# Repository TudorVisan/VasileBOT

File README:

VasileBOT! LineFollower extraordinaire!

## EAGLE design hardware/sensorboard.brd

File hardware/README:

v1.0
    - Complete BOM available at
      https://docs.google.com/spreadsheets/d/1lKYWt8WgzWd33CoD_yIm1lVHJigqv4kNXPXV9A-a3yk/edit?usp=sharing

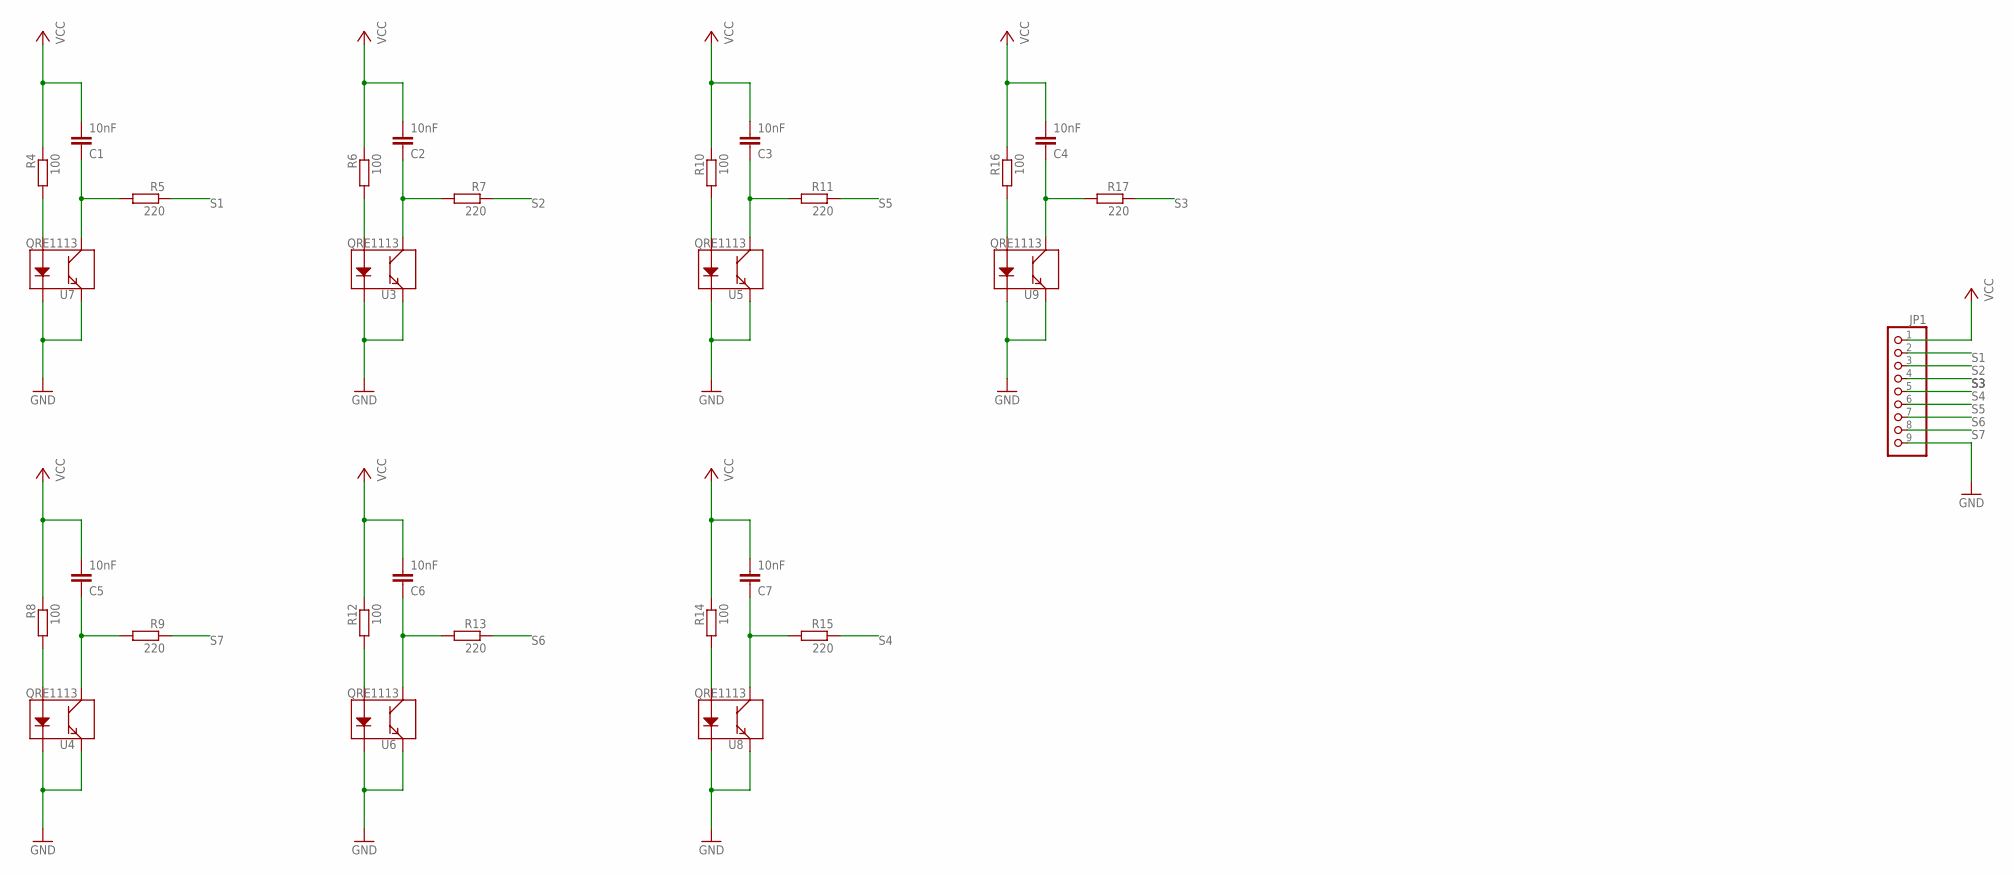
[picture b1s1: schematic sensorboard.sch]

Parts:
C1, C2, C3, C4, C5, C6, C7: 10nF; C0805K
JP1: PINHD-1X9; 1X09
R4, R6, R8, R10, R12, R14, R16: 100; M0805
R5, R7, R9, R11, R13, R15, R17: 220; M0805
U3, U4, U5, U6, U7, U8, U9: QRE1113

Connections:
GND: JP1.9, U3.2 (K), U3.4 (E), U4.2 (K), U4.4 (E), U5.2 (K), U5.4 (E), U6.2 (K), U6.4 (E), U7.2 (K), U7.4 (E), U8.2 (K), U8.4 (E), U9.2 (K), U9.4 (E)
unnamed: C1.1, R5.2, U7.3 (C)
unnamed: C2.1, R7.2, U3.3 (C)
unnamed: C3.1, R11.2, U5.3 (C)
unnamed: C4.1, R17.2, U9.3 (C)
unnamed: C7.1, R15.2, U8.3 (C)
unnamed: C6.1, R13.2, U6.3 (C)
unnamed: C5.1, R9.2, U4.3 (C)
unnamed: R4.2, U7.1 (A)
unnamed: R6.2, U3.1 (A)
unnamed: R8.2, U4.1 (A)
unnamed: R10.2, U5.1 (A)
unnamed: R12.2, U6.1 (A)
unnamed: R14.2, U8.1 (A)
unnamed: R16.2, U9.1 (A)
S1: JP1.2, R5.1
S2: JP1.3, R7.1
S3: JP1.4, R17.1
S4: JP1.5, R15.1
S5: JP1.6, R11.1
S6: JP1.7, R13.1
S7: JP1.8, R9.1
VCC: C1.2, C2.2, C3.2, C4.2, C5.2, C6.2, C7.2, JP1.1, R4.1, R6.1, R8.1, R10.1, R12.1, R14.1, R16.1

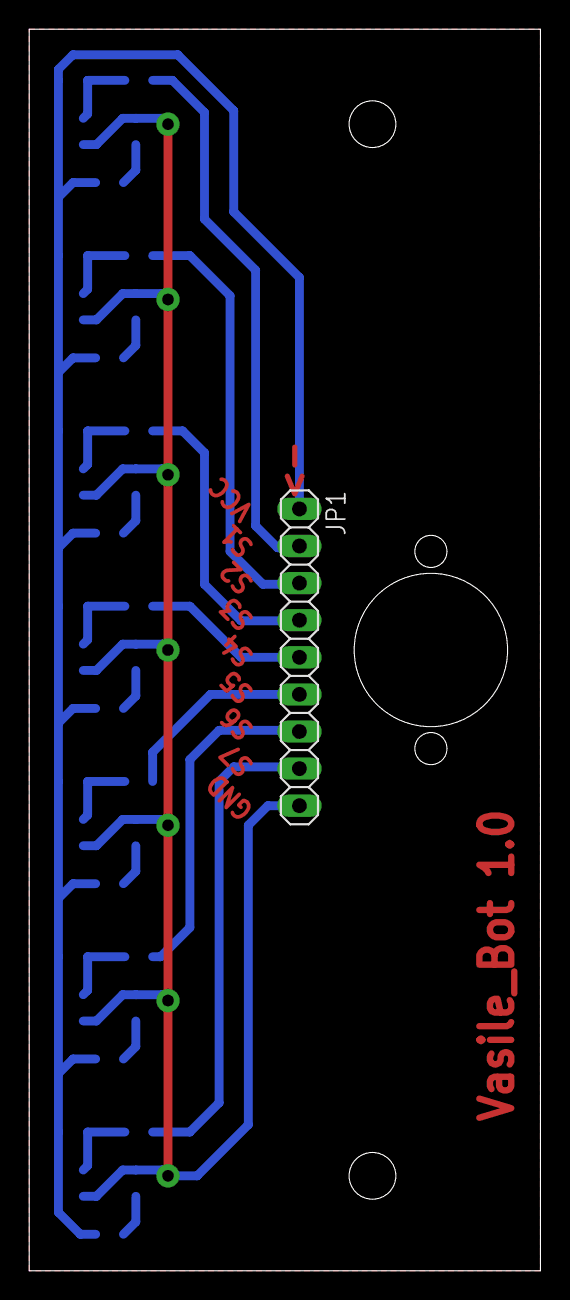
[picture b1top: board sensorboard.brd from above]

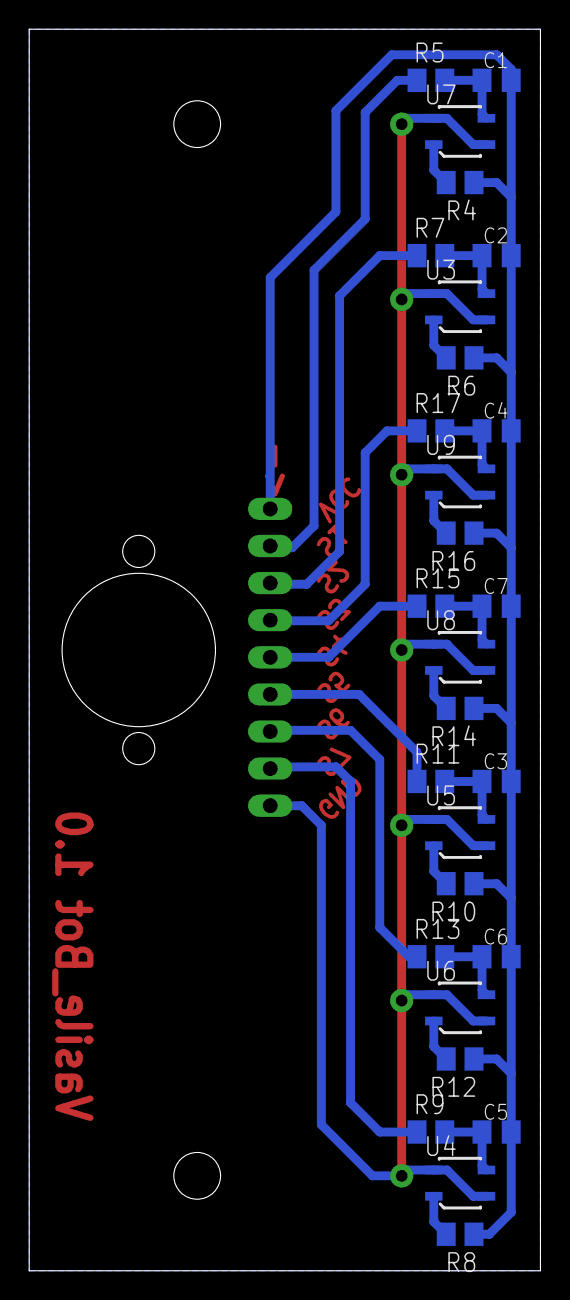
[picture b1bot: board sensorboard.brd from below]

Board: 2 copper layers, 35.0 x 85.0 mm, 29 parts (28 on the bottom side), 23 nets.

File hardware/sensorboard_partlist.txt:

Partlist

Exported from sensorboard.sch at 08/11/2016 20:00

EAGLE Version 7.6.0 Copyright (c) 1988-2016 CadSoft

Assembly variant: 

Part     Value          Device     Package  Library          Sheet

C1       10nF           C-EUC0805K C0805K   resistor         1
C2       10nF           C-EUC0805K C0805K   resistor         1
C3       10nF           C-EUC0805K C0805K   resistor         1
C4       10nF           C-EUC0805K C0805K   resistor         1
C5       10nF           C-EUC0805K C0805K   resistor         1
C6       10nF           C-EUC0805K C0805K   resistor         1
C7       10nF           C-EUC0805K C0805K   resistor         1
JP1                     PINHD-1X9  1X09     pinhead          1
R4       100            R-EU_M0805 M0805    resistor         1
R5       220            R-EU_M0805 M0805    resistor         1
R6       100            R-EU_M0805 M0805    resistor         1
R7       220            R-EU_M0805 M0805    resistor         1
R8       100            R-EU_M0805 M0805    resistor         1
R9       220            R-EU_M0805 M0805    resistor         1
R10      100            R-EU_M0805 M0805    resistor         1
R11      220            R-EU_M0805 M0805    resistor         1
R12      100            R-EU_M0805 M0805    resistor         1
R13      220            R-EU_M0805 M0805    resistor         1
R14      100            R-EU_M0805 M0805    resistor         1
R15      220            R-EU_M0805 M0805    resistor         1
R16      100            R-EU_M0805 M0805    resistor         1
R17      220            R-EU_M0805 M0805    resistor         1
U3       QRE1113        QRE1113    QRE1113  SparkFun-Sensors 1
U4       QRE1113        QRE1113    QRE1113  SparkFun-Sensors 1
U5       QRE1113        QRE1113    QRE1113  SparkFun-Sensors 1
U6       QRE1113        QRE1113    QRE1113  SparkFun-Sensors 1
U7       QRE1113        QRE1113    QRE1113  SparkFun-Sensors 1
U8       QRE1113        QRE1113    QRE1113  SparkFun-Sensors 1
U9       QRE1113        QRE1113    QRE1113  SparkFun-Sensors 1

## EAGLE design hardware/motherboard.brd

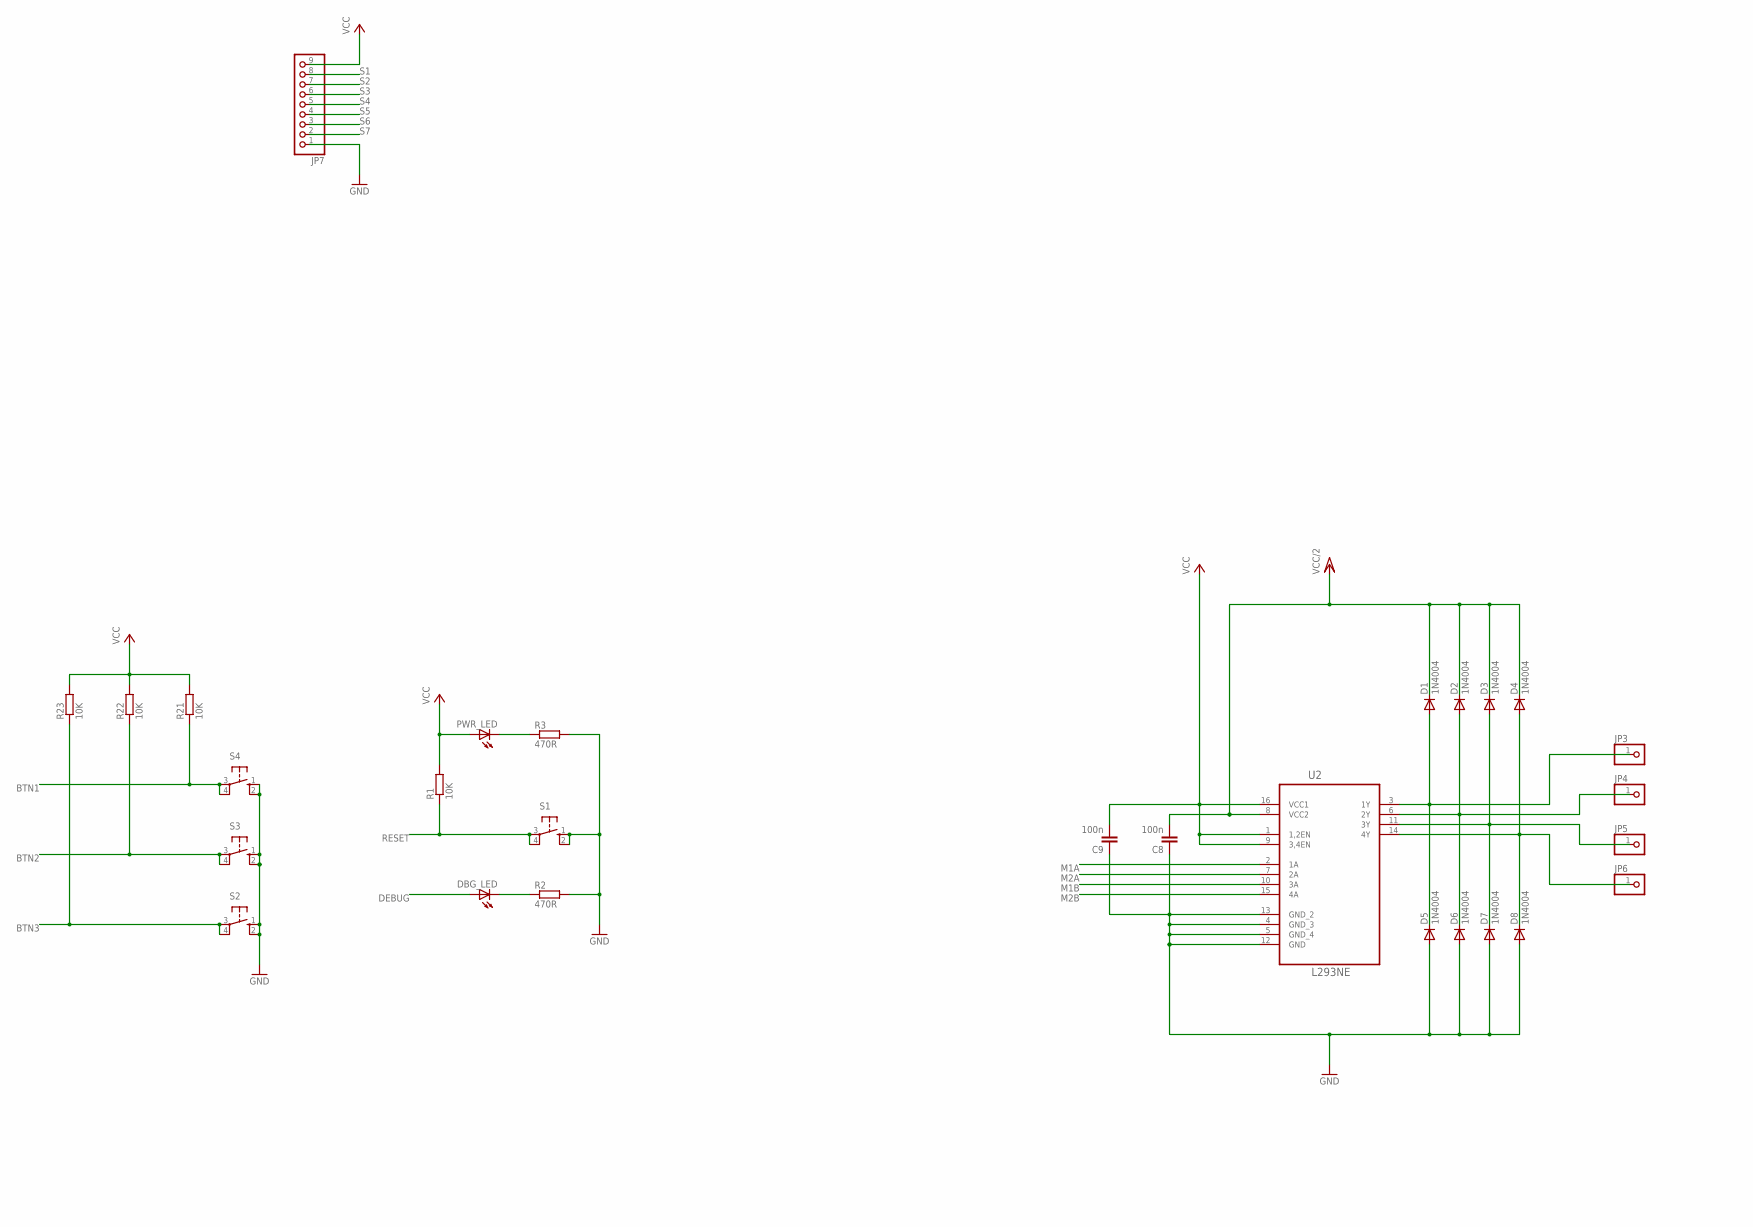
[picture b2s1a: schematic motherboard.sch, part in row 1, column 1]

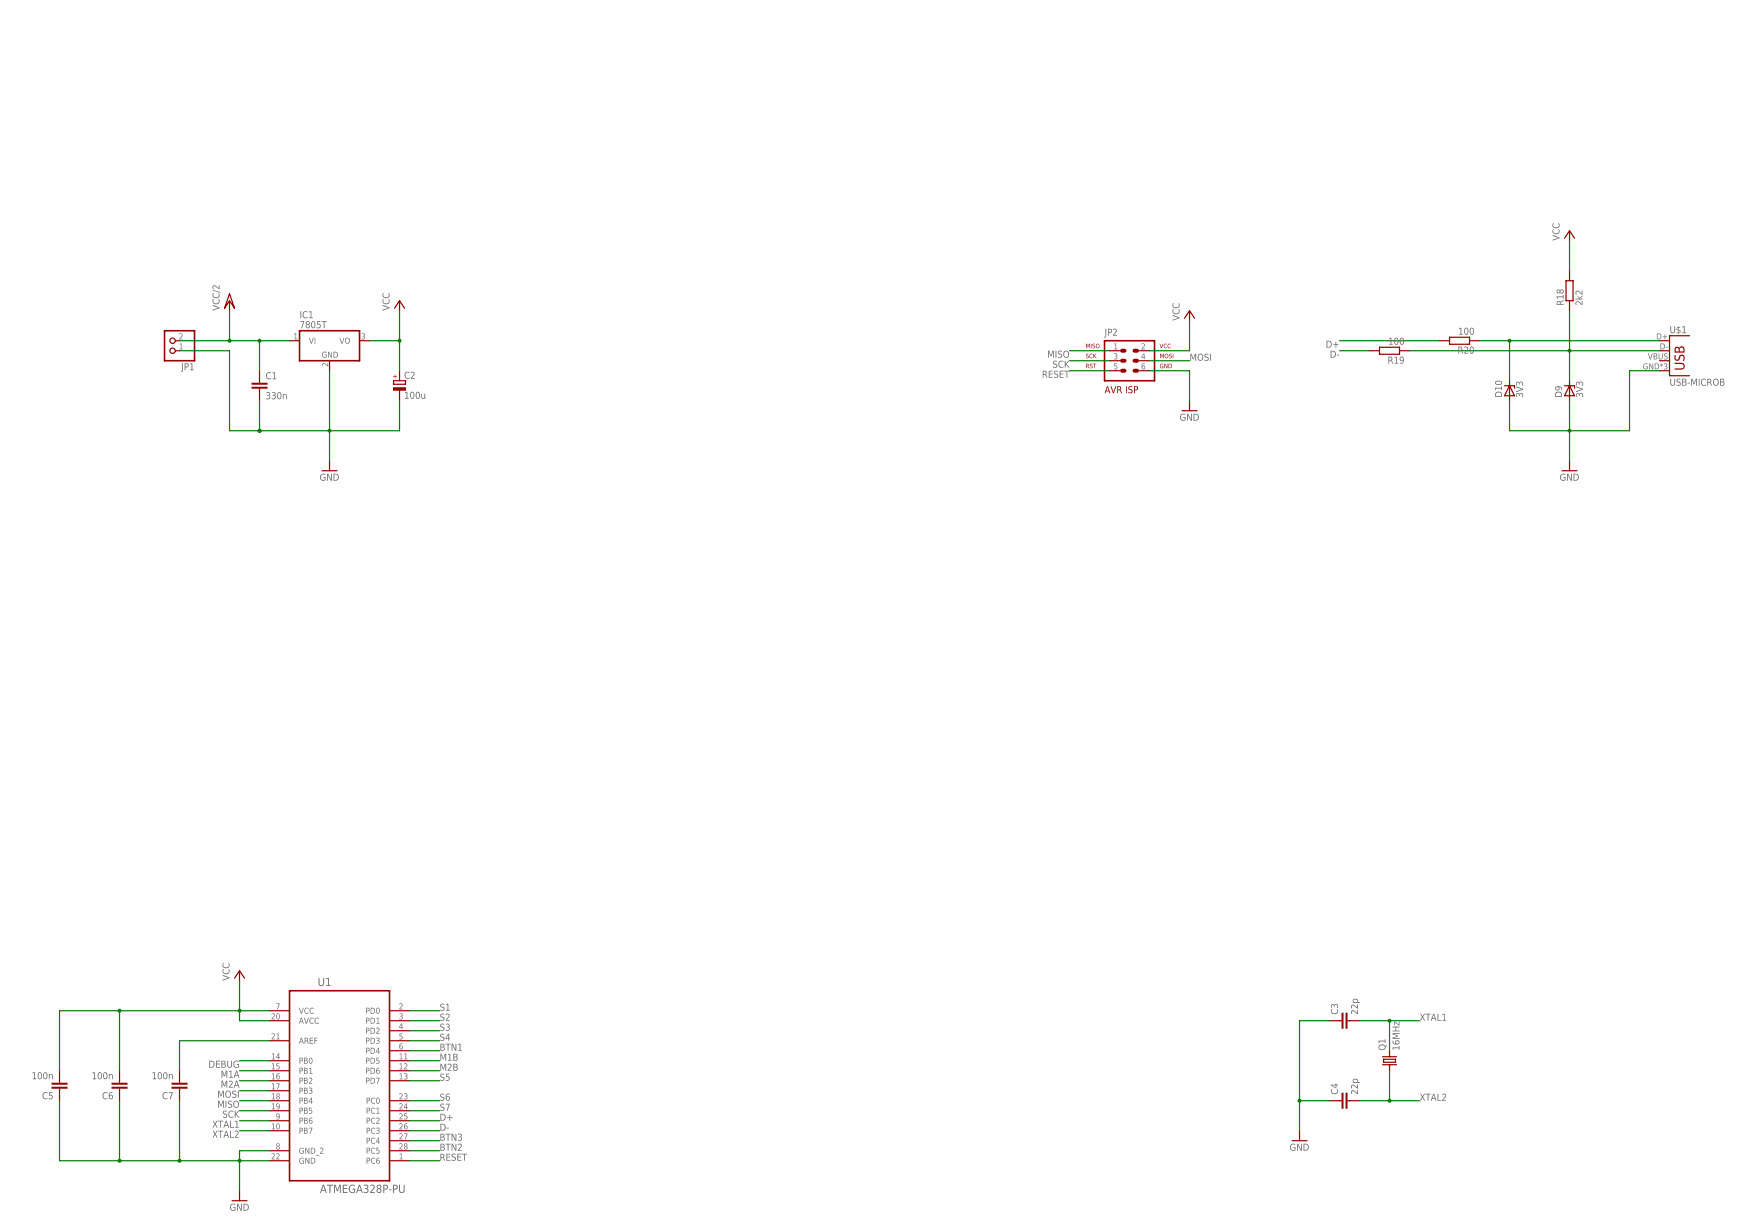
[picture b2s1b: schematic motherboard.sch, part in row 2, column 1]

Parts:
C1: 330n; C0805K
C2: 100u; E2,5-5
C3, C4: 22p; C0805K
C5, C6, C7, C8, C9: 100n; C0805K
D1, D2, D3, D4, D5, D6, D7, D8: 1N4004; DO41-10
D9, D10: 3V3; DO41Z10
DBG_LED: LED5MM
IC1: 7805T; TO220H
JP1: PINHD-1X2; 1X02
JP2: AVR-ISP-6VERT; AVR-ISP-6
JP3, JP4, JP5, JP6: PINHD-1X1; 1X01
JP7: PINHD-1X9; 1X09
PWR_LED: LED5MM
Q1: 16MHz; HC49/S
R1, R21, R22, R23: 10K; M0805
R2, R3: 470R; M0805
R18: 2k2; M0805
R19, R20: 100; M0805
S1, S2, S3, S4: 10-XX; B3F-10XX
U1: ATMEGA328P-PU; DIP254P762X457-28
U2: L293NE; DIP254P762X508-16
U$1: USB-MICROB

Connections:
BTN1: R21.1, S4.3, S4.4 (P1), U1.6 (PD4)
BTN2: R22.1, S3.3, S3.4 (P1), U1.28 (PC5)
BTN3: R23.1, S2.3, S2.4 (P1), U1.27 (PC4)
D+: R20.2, U1.25 (PC2)
D-: R19.2, U1.26 (PC3)
DEBUG: DBG_LED.A, U1.14 (PB0)
GND: C1.2, C2.-, C3.1, C4.1, C5.1, C6.1, C7.1, C8.1, C9.1, D5.A, D6.A, D7.A, D8.A, D9.A, D10.A, IC1.2 (GND), JP1.1, JP2.6, JP7.1, R2.2, R3.2, S1.1 (S), S1.2 (S1), S2.1 (S), S2.2 (S1), S3.1 (S), S3.2 (S1), S4.1 (S), S4.2 (S1), U1.8 (GND_2), U1.22 (GND), U2.4 (GND_3), U2.5 (GND_4), U2.12 (GND), U2.13 (GND_2), U$1.GND, U$1.MT1 (GND), U$1.MT2 (GND)
M1A: U1.15 (PB1), U2.2 (1A)
M1B: U1.11 (PD5), U2.10 (3A)
M2A: U1.16 (PB2), U2.7 (2A)
M2B: U1.12 (PD6), U2.15 (4A)
MISO: JP2.1, U1.18 (PB4)
MOSI: JP2.4, U1.17 (PB3)
unnamed: PWR_LED.K (C), R3.1
unnamed: DBG_LED.K (C), R2.1
unnamed: C7.2, U1.21 (AREF)
unnamed: D1.A, D5.C, JP3.1, U2.3 (1Y)
unnamed: D2.A, D6.C, JP4.1, U2.6 (2Y)
unnamed: D3.A, D7.C, JP5.1, U2.11 (3Y)
unnamed: D4.A, D8.C, JP6.1, U2.14 (4Y)
unnamed: D9.C, R18.1, R19.1, U$1.D-
unnamed: D10.C, R20.1, U$1.D+
RESET: JP2.5, R1.1, S1.3, S1.4 (P1), U1.1 (PC6)
S1: JP7.8, U1.2 (PD0)
S2: JP7.7, U1.3 (PD1)
S3: JP7.6, U1.4 (PD2)
S4: JP7.5, U1.5 (PD3)
S5: JP7.4, U1.13 (PD7)
S6: JP7.3, U1.23 (PC0)
S7: JP7.2, U1.24 (PC1)
SCK: JP2.3, U1.19 (PB5)
VCC: C2.+, C5.2, C6.2, C9.2, IC1.3 (VO), JP2.2, JP7.9, PWR_LED.A, R1.2, R18.2, R21.2, R22.2, R23.2, U1.7 (VCC), U1.20 (AVCC), U2.1 (1,2EN), U2.9 (3,4EN), U2.16 (VCC1)
VCC/2: C1.1, C8.2, D1.C, D2.C, D3.C, D4.C, IC1.1 (VI), JP1.2, U2.8 (VCC2)
XTAL1: C3.2, Q1.2, U1.9 (PB6)
XTAL2: C4.2, Q1.1, U1.10 (PB7)

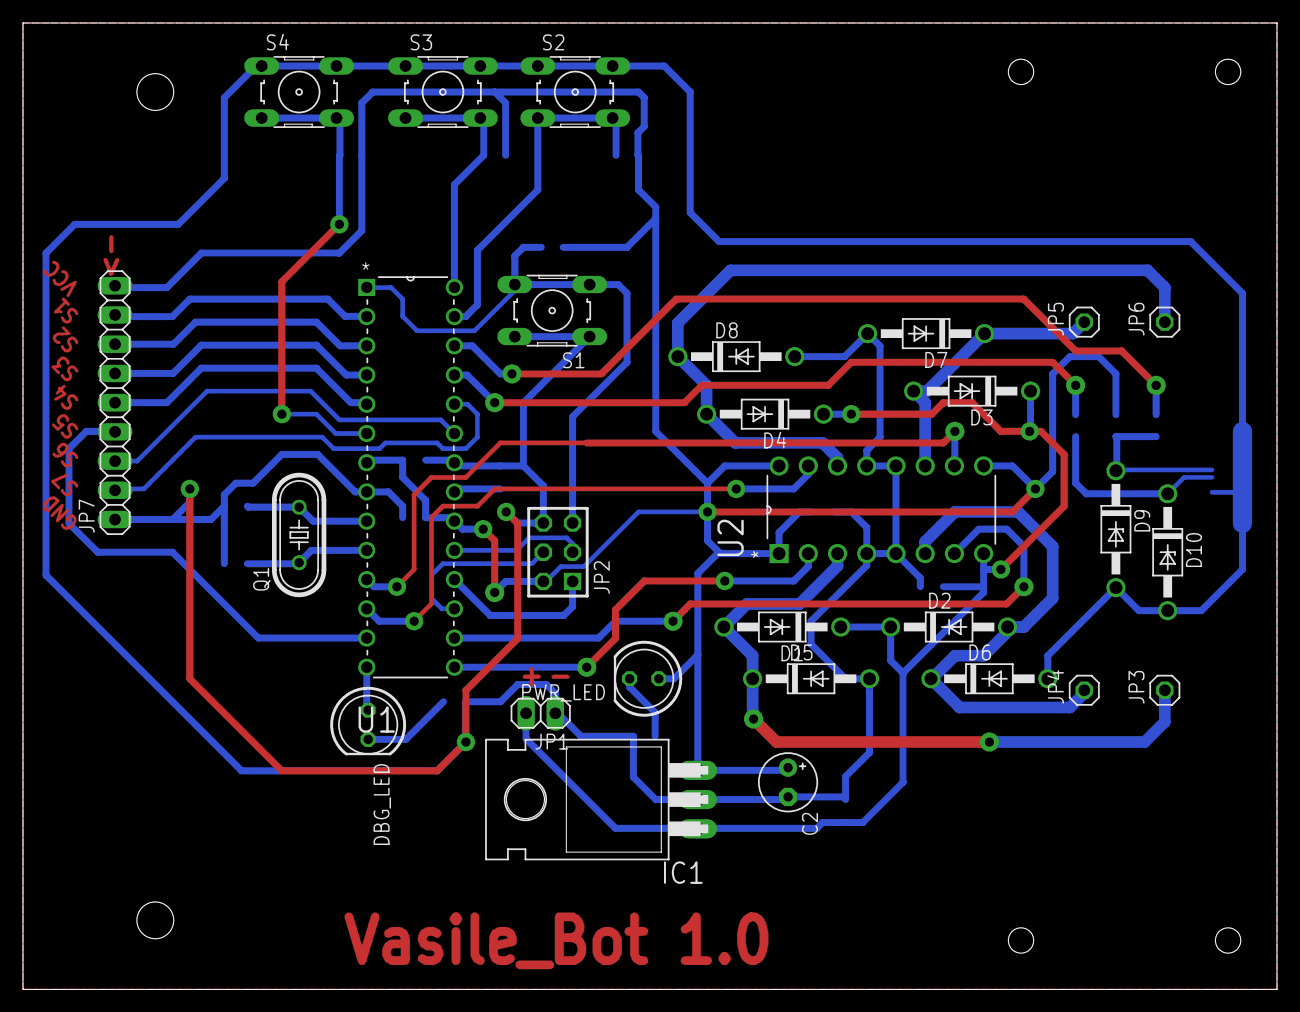
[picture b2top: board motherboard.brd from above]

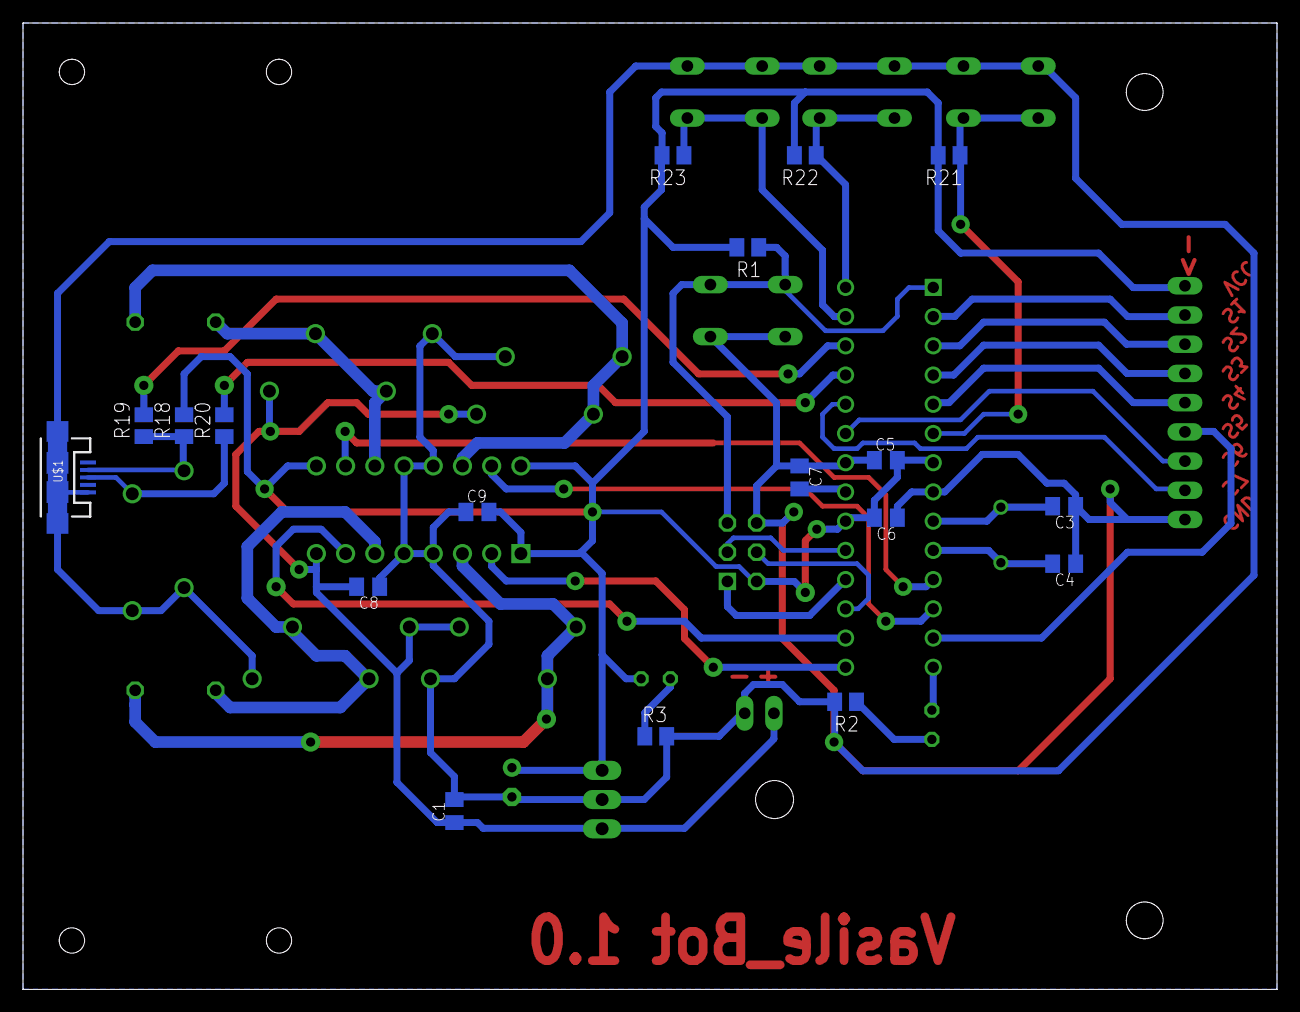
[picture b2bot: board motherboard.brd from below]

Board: 2 copper layers, 109.0 x 84.0 mm, 46 parts (18 on the bottom side), 35 nets.

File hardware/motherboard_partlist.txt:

Partlist

Exported from motherboard.brd at 08/11/2016 20:19

EAGLE Version 7.6.0 Copyright (c) 1988-2016 CadSoft

Assembly variant:

Part     Value          Package           Library             Position (mm)         Orientation

C1       330n           C0805K            resistor            (71.5 15.5)           MR90
C2       100u           E2,5-5            resistor            (66.5 18)             R270
C3       22p            C0805K            resistor            (18.5 42)             MR180
C4       22p            C0805K            resistor            (18.5 37)             MR180
C5       100n           C0805K            resistor            (34 46)               MR0
C6       100n           C0805K            resistor            (34 41)               MR180
C7       100n           C0805K            resistor            (41.5 44.5)           MR270
C8       100n           C0805K            resistor            (79 35)               MR180
C9       100n           C0805K            resistor            (69.5 41.5)           MR0
D1       1N4004         DO41-10           diode               (66 31.5)             R180
D2       1N4004         DO41-10           diode               (80.5 31.5)           R0
D3       1N4004         DO41-10           diode               (82.5 52)             R180
D4       1N4004         DO41-10           diode               (64.5 50)             R180
D5       1N4004         DO41-10           diode               (68.5 27)             R0
D6       1N4004         DO41-10           diode               (84 27)               R0
D7       1N4004         DO41-10           diode               (78.5 57)             R180
D8       1N4004         DO41-10           diode               (62 55)               R0
D9       3V3            DO41Z10           diode               (95 40)               R270
D10      3V3            DO41Z10           diode               (99.5 38)             R270
DBG_LED                 LED5MM            led                 (30 23)               R270
IC1      7805T          TO220H            linear              (48.5 16.5)           R90
JP1                     1X02              pinhead             (45 24)               R180
JP2      AVR-ISP-6VERT  AVR-ISP-6         avr-7               (46.5 38)             R90
JP3                     1X01              pinhead             (99.25 26)            R90
JP4                     1X01              pinhead             (92.25 26)            R90
JP5                     1X01              pinhead             (92.25 58)            R90
JP6                     1X01              pinhead             (99.25 58)            R90
JP7                     1X09              pinhead             (8 51)                R90
PWR_LED                 LED5MM            led                 (54 27)               R180
Q1       16MHz          HC49/S            crystal             (24 39.5)             R90
R1       10K            M0805             resistor            (46 64.5)             MR180
R2       470R           M0805             resistor            (37.5 25)             MR180
R3       470R           M0805             resistor            (54 22)               MR0
R18      2k2            M0805             resistor            (95 49)               MR90
R19      100            M0805             resistor            (98.5 49)             MR90
R20      100            M0805             resistor            (91.5 49)             MR90
R21      10K            M0805             resistor            (28.5 72.5)           MR180
R22      10K            M0805             resistor            (41 72.5)             MR180
R23      10K            M0805             resistor            (52.5 72.5)           MR180
S1                      B3F-10XX          switch-omron        (46 59)               R180
S2                      B3F-10XX          switch-omron        (48 78)               R0
S3                      B3F-10XX          switch-omron        (36.5 78)             R0
S4                      B3F-10XX          switch-omron        (24 78)               R0
U$1      USB-MICROB     USB-MICROB        SparkFun-Connectors (106 44.5)            MR270
U1       ATMEGA328P-PU  DIP254P762X457-28 untitled            (37.5 28)             R0
U2       L293NE         DIP254P762X508-16 untitled            (83.5 45.5)           R90

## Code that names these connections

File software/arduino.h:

/* Debug LED conectat pe portul PB0 */
#define DEBUG_LED_DDR	DDRB
#define DEBUG_LED_PIN	PINB
#define DEBUG_LED_PORT	PORTB
#define DEBUG_LED		PB0

/* Buton on/off(BTN1) conectat pe portul PD4/PB4 - pin 8 */
#define BTN1_DDR		DDRB
#define BTN1_PIN		PINB
#define BTN1_PORT		PORTB
#define BTN1			PB4
#define BTN1_PCINT		PCINT4
#define BTN1_PCINT_IE	PCIE0
#define BTN1_PCMSK 		PCMSK0

/* Buton lower frequency(BTN2) conectat pe portul PC5/PB5 - pin 9 */
#define BTN2_DDR		DDRB
#define BTN2_PIN		PINB
#define BTN2_PORT		PORTB
#define BTN2			PB5
#define BTN2_PCINT		PCINT5
#define BTN2_PCINT_IE	PCIE0
#define BTN2_PCMSK 		PCMSK0

/* Buton higher frequency(BTN3) conectat pe portul PC4/PB6 - pin 10 */
#define BTN3_DDR		DDRB
#define BTN3_PIN		PINB
#define BTN3_PORT		PORTB
#define BTN3			PB6
#define BTN3_PCINT		PCINT6
#define BTN3_PCINT_IE	PCIE0
#define BTN3_PCMSK 		PCMSK0

/* senzorul S1 conectat pe pinul PD0/PF7 - pin A0 */
#define S1 			PF7
#define S1_DDR 		DDRF
#define S1_PIN 		PINF
#define S1_PORT 	PORTF

/* senzorul S2 conectat pe pinul PD1/PF6 - pin A1 */
#define S2 			PF6
#define S2_DDR 		DDRF
#define S2_PIN 		PINF
#define S2_PORT 	PORTF

/* senzorul S3 conectat pe pinul PD2/PF5 - pin A2 */
#define S3 			PF5
#define S3_DDR 		DDRF
#define S3_PIN 		PINF
#define S3_PORT 	PORTF

/* senzorul S4 conectat pe pinul PD3/PF4 - pin A3 */
#define S4 			PF4
#define S4_DDR 		DDRF
#define S4_PIN 		PINF
#define S4_PORT 	PORTF

/* senzorul S5 conectat pe pinul PD5/PF1 - pin A4 */
#define S5 			PF1
#define S5_DDR 		DDRF
#define S5_PIN 		PINF
#define S5_PORT 	PORTF

/* senzorul S6 conectat pe pinul PC0/PF0 - pin A5 */
#define S6 			PF0
#define S6_DDR 		DDRF
#define S6_PIN 		PINF
#define S6_PORT 	PORTF

/* senzorul S7 conectat pe pinul PC1/PD4 - pin 4 */
#define S7 			PD4
#define S7_DDR 		DDRD
#define S7_PIN 		PIND
#define S7_PORT 	PORTD

/* Motor 1 output A conectat la PB1/PC6 - pin 5 */
#define M1A			PC6
#define M1A_PIN		PINC
#define M1A_DDR		DDRC
#define M1A_PORT	PORTC

/* Motor 2 output A conectat la PB2/PC7 - pin 13 */
#define M2A			PC7
#define M2A_PIN		PINC
#define M2A_DDR		DDRC
#define M2A_PORT	PORTC

/* Motor 1 output B conectat la PD5/PD7 - pin 6 */
#define M1B			PD7
#define M1B_PIN		PIND
#define M1B_DDR		DDRD
#define M1B_PORT	PORTD

/* Motor 2 output B conectat la PD6/PD0 - pin 3 */
#define M2B			PD0
#define M2B_PIN		PIND
#define M2B_DDR		DDRD
#define M2B_PORT	PORTD

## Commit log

2016-04-27 Initial commit.
2016-04-27 Added README.
2016-04-27 Added source for VasileBot main program.
2016-04-27 Added Makefile.
2016-05-18 added hardware
2016-05-18 Fixed Makefile.
2016-05-18 Added button functions.
    LED button frequencies may now vary.
2016-05-18 Added macros and flags in code.
    Improved code.
    Added new things to TODO list.
    Requested datasheet.
2016-05-18 Removed and renamed hardware files.
2016-05-18 Added a new board wich contains sensors.
    Modified motherboard and removed sensors. Moved them to a new separate
    board.
2016-05-18 Added ATmega328P datasheet.
2016-05-18 Added intrerrupts to software.
    Added intrerrupt specific macros.
    Added IO_init function.
2016-05-18 Added pin header to motherboard. Fixed all wire connection from motherboard.
2016-05-25 Added functions to initialize and read sensors.
2016-05-25 Fixed compilation errors.
2016-05-25 Added motor init and macros.
2016-05-25 Added capacitors to sensor board. Fixed routing.
2016-09-29 Prepared stage for porting to Arduino UNO.
2016-09-29 Added config target to makefile for configuring the board to be used.
2016-09-29 Added Arduino UNO Rev.3 schematics for reference.
2016-09-29 Added header files.
2016-10-11 Removed schematics for Arduino Uno. Added schematics for Arduino Leonardo and datasheet for ATmega32U4.
2016-10-11 Removed misc folder.
2016-10-11 Removed software TODO file.
2016-10-11 Fixed motherboard errors.
2016-10-11 Added motherboard length measurement.
2016-10-11 Added dimension to sensorboard.
2016-10-11 Added halls to motherboard. Added dimension.
2016-10-11 Modified header and makefile for Arduino test.
2016-10-18 Added ball caster. Added halls for ball caster. Fixed mounting halls.
2016-10-18 Fixed motors space. Added motors halls.
2016-10-18 Added an arduino only source file for testing and upload target to Makefile
2016-10-24 Add files via upload
    Added links for ball caster, motors, wheels and battery.
2016-10-24 Added links for motors, battery, wheels and ball caster.
2016-11-01 Added custom MCU, board name and upload command for each board. Removed backup makefile. Added bootloadHID uploader.
2016-11-01 Removed secondary firmware file.
2016-11-01 Made 2 source files for different boards and board library.
2016-11-01 Fixed makefile. Fixed compilation errors.
2016-11-01 Fixed LED blinking for Arduino Leonardo.
2016-11-08 Added partlists for boards.
2016-11-08 Disabled USB controller for Arduino Leonardo.
2016-11-13 Remove component list. Added link to BOM in a README file for hardware.
2016-11-13 Beautified sensorboard and motherboard schematics. Fixed motherboard angle error.
2016-11-15 Added volatile variables, tested buttons and sensors, added power led for button3.
2016-11-22 Modified motors initialisation for Arduino Board.
2016-12-20 Added pdf files to be ignored.

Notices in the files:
parts and their libraries:
SparkFun-Connectors: Licensing: Creative Commons ShareAlike 4.0 International - https://creativecommons.org/licenses/by-sa/4.0
